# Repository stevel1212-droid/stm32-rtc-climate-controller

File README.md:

# stm32-rtc-climate-controller

Kicad project (Hardware) and Platform IO project (Firmware) of an STM32-based board climate controller utilizing an RTC module for time-scheduled environmental reading of temperature/humidity with SHT30 sensor and optional small relay for control.

I've ordered the PCBA (SMT assembly only) from JLCPCB and it costs around 62$  for 2 assembled and 3 empty boards with  coupon:

### 🛠️ Tools & Plugins Used:

#### Hardware (KiCad)
* **Footprints & Symbols:** To quickly download components from JLCPCB, I used the [easyeda2kicad](https://github.com/uPesy/easyeda2kicad.py) tool.
* **Manufacturing Files:** To create the fabrication files for PCB and SMD assembly via JLCPCB, I used the [kicad-jlcpcb-tools](https://github.com/bouni/kicad-jlcpcb-tools) external plugin.

#### Firmware (Software)
* **IDE:** Developed using [Visual Studio Code](https://code.visualstudio.com/) with the **PlatformIO IDE** extension.
* **Framework:** Written in C/C++ using the **Arduino Framework** for the STM32F103C8 microcontroller.
* **Peripherals:** Includes support for an SSD1306 OLED display using Adafruit libraries.

---

### 🛒 Hardware Components & Equipment Used:

If you want to build or debug this project, here is the specific hardware and equipment used:

* **Display:** [0.96 inch OLED I2C Display SSD1306](https://www.amazon.com/dp/B0D2RMQQHR?ref_=ppx_hzsearch_conn_dt_b_fed_asin_title_3) - Used for showing temperature, humidity, and time data.
* **RTC Battery:** [Energizer CR2032 Lithium Battery](https://www.amazon.com/dp/B009108SGS?ref=nb_sb_ss_w_as-reorder_k1_1_5&th=1) - Provides backup power to the RTC module to keep time when the main board is powered off.
* **Debugger:** [ST-Link V2 Programmer/Debugger](https://www.amazon.com/dp/B0C9PKJF2T?ref_=ppx_hzsearch_conn_dt_b_fed_asin_title_1&th=1) - Used for flashing the firmware and debugging the STM32.
* **Soldering Iron:** [Pinecil Smart Soldering Iron (BB2)](https://www.amazon.com/dp/B08PZBPXLZ?ref_=ppx_hzsearch_conn_dt_b_fed_asin_title_1&th=1) - Highly recommended portable soldering iron used for assembling the board.

## 🚀 First-Time Setup & Firmware Upload

Follow these steps to flash the firmware and configure the board for the first time:

### 1. Hardware Configuration (Boot Pins)
* Ensure that both **BOOT0** and **BOOT1** jumpers/pins are set to a **logic low** state (GND).

### 2. Connecting the Debugger
* Connect your **ST-Link V2** debugger to the **H1** connector on the board using the following pins: **SWDIO**, **SWCLK**, **3.3V**, and **GND**:

* ⚠️ **CRITICAL:** Do NOT connect the USB-C cable to the board while the debugger is connected and powering the system.

### 3. PlatformIO Configuration (`platformio.ini`)
Open your `platformio.ini` file and adjust the upload settings. You need to enable the ST-Link protocol and comment out the serial configurations:

```ini
# Set the upload protocol to ST-Link
upload_protocol = stlink

# Comment out the serial upload lines
; upload_protocol = serial
; upload_port = COM3
```

### 4. Flashing the Firmware
Plug the ST-Link V2 debugger into your computer's USB port.

In VS Code / PlatformIO, click the Upload button (the right-arrow icon in the bottom status bar) to flash the code to your STM32.

### 5. Setting the Date and Time (RTC Configuration)
Once the firmware is uploaded, disconnect the ST-Link V2 debugger from the board.

Connect the board to your computer using a USB-C cable.

Ensure you have the CP2102 driver installed on your computer so the USB-to-UART bridge is recognized.

Open the Serial Monitor in PlatformIO.

Send the current time and date through the serial terminal using the following exact format: HH:MM:SS DD:MM:YYYY (e.g., 14:30:00 15:06:2026).

### 🎁 Bonus: Serial Flashing (Alternative Method)
Note: This option is only available after the initial first-time flash.
If you prefer to flash future firmware updates directly via USB (Serial) instead of using the ST-Link debugger,
follow these steps:

* Set the BOOT0 pin/jumper to a logic high state (3.3V).
* Press the RESET button on the board to enter the embedded bootloader.
* In your platformio.ini file, switch the comments to enable serial upload:
```Ini
; upload_protocol = stlink
upload_protocol = serial
```
* Click the Upload button in PlatformIO.
* ⚠️ IMPORTANT: Once the upload is finished, you must set the BOOT0 pin back to a logic low state (GND) and press the RESET          button again. Otherwise, the newly uploaded program will not execute upon boot.

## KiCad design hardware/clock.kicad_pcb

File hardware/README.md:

here is the Kicad project files

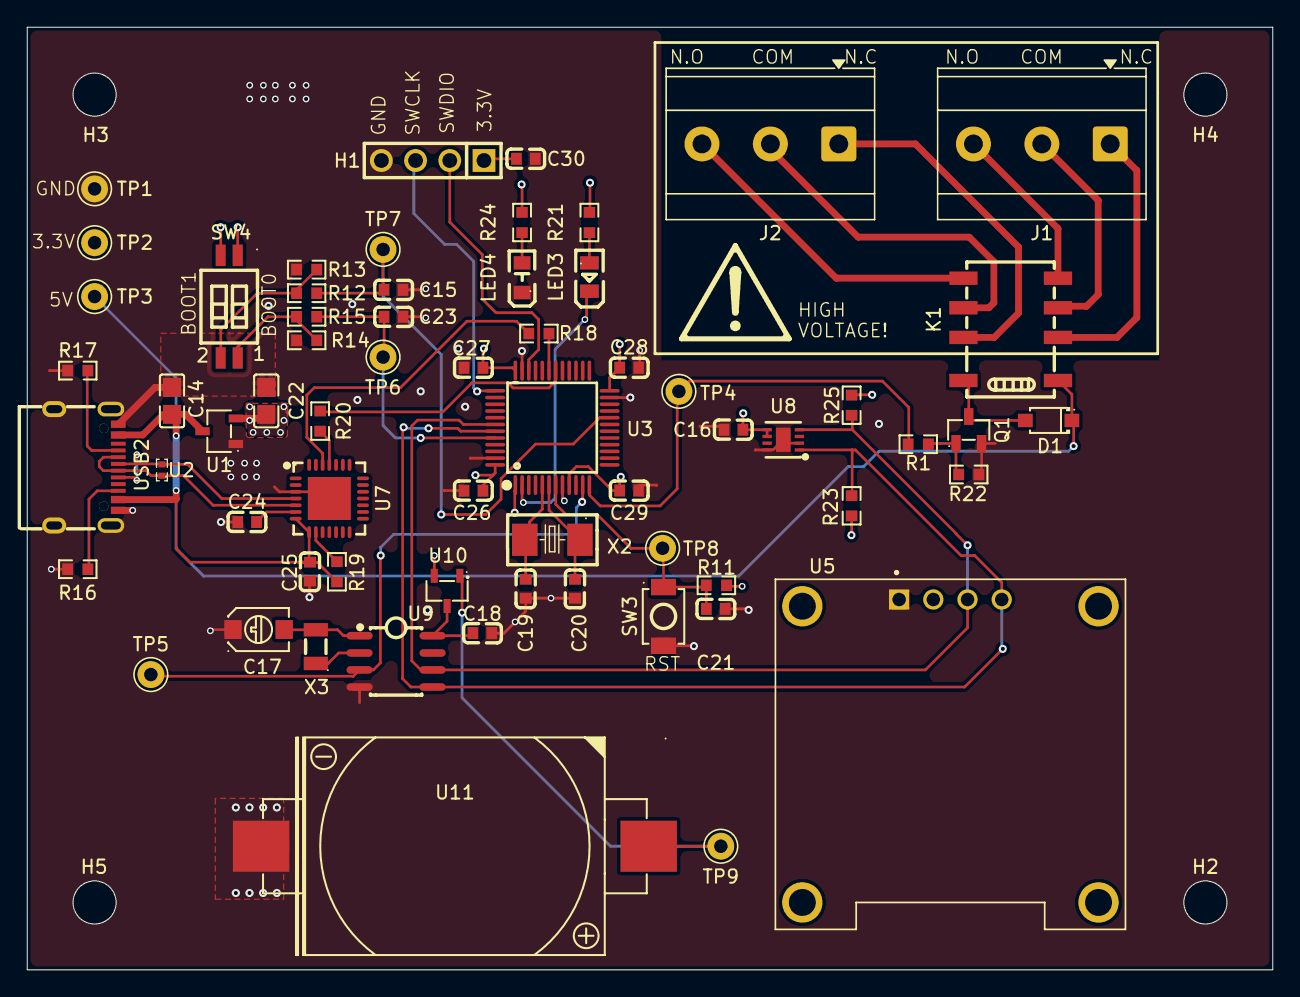
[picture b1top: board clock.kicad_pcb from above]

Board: 4 copper layers, 92.5 x 70.0 mm, 68 parts (0 on the bottom side), 41 nets.

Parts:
C14, C22: CL21B105KBFNNNE; C0805
C15, C16, C18, C21, C23, C24, C25, C26, C27, C28, C29, C30: CC0603KRX7R9BB104; C0603
C17: STC3MD20-T1; CAP-SMD_L4.5-W3.2_STC3MD20-T1
C19, C20: CL10C200JB8NNNC; C0603
D1: 1N4148W_C81598; SOD-123F_L2.7-W1.6-LS3.8-RD
H1: PZ254V-11-04P_C2691448; HDR-TH_4P-P2.54-V-M
H2, H3, H4, H5: MountingHole; MountingHole_3.2mm_M3
J1, J2: Screw_Terminal_01x03; TerminalBlock_MetzConnect_Type073_RT02603HBLU_1x03_P5.08mm_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
K1: G6K-2F-Y-DC5; RELAY-SMD_G6K-2F-X-XX
LED3: 0805G; LED0805-R-RD
LED4: FC-2012HRK-620D; LED0805-RD
Q1: 2N7002; SOT-23-3_L2.9-W1.3-P1.90-LS2.4-BR
R1: 0603WAF1000T5E; R0603
R11, R19: 0603WAF1002T5E; R0603
R12, R15, R18, R20, R21, R24: 0603WAF1001T5E; R0603
R13, R14, R22: 0603WAF1003T5E; R0603
R16, R17, R23, R25: 0603WAF5101T5E; R0603
SW3: TS-1088-AR02016; SW-SMD_L3.9-W3.0-P4.45
SW4: DSHP02TS-S; SW-SMD_DSHP02TS-S
TP1, TP2, TP3, TP4, TP5, TP6, TP7, TP8, TP9: TestPoint; Pin_D1.0mm_L10.0mm
U1: XC6206P332MR; SOT-23-3_L2.9-W1.6-P1.90-LS2.8-BR
U2: H3V3U10B; DFN1006-2L-BI
U3: STM32F103C8T6; LQFP-48_L7.0-W7.0-P0.50-LS9.0-BL
U5: DM-OLED096-636; MODULE_DM-OLED096-636
U7: CP2102-GMR; WQFN-28_L5.0-W5.0-P0.50-BL-EP3.2
U8: SHT30-DIS-B; DFN-8_L2.5-W2.5-P0.50-BL-EP
U9: PCF8563T/5,518; SOIC-8_L5.0-W4.0-P1.27-LS6.0-BL
U10: BAT54C_C22466350; SOT-23-3_L2.9-W1.3-P1.90-LS2.8-BR
U11: CR2032-BS-6; BAT-TH_CR2032-BS-6-1
USB2: TYPE-C 16PIN 2MD; USB-C-SMD_TYPE-C-6PIN-2MD-073
X2: X50328MSB2GI; CRYSTAL-SMD_L5.0-W3.2
X3: Q13FC1350000400; FC-135R_L3.2-W1.5

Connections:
+3.3V: C16.2, C22.2, C26.2, C27.2, C28.2, C29.2, C30.1, H1.1, R11.2, R21.2, R23.2, R24.2, R25.2, SW4.1, SW4.2, TP2.1 (1_1), U1.2 (Vout), U3.1 (VBAT), U3.9 (VDDA), U3.24 (VDD_1), U3.36 (VDD_2), U3.48 (VDD_3), U5.2 (VCC_IN), U8.5 (VDD), U8.6 (nRESET), U10.2 (A)
+5V: C14.2, C25.2, D1.1 (K), K1.1, R19.1, TP3.1 (1_1), U1.3 (Vin), U7.7 (REGIN), U7.8 (VBUS), USB2.2 (VBUS), USB2.11 (VBUS)
/mcu/BOOT0: C23.2, R15.2, TP6.1 (1_1), U3.44 (BOOT0)
/mcu/BOOT1: C15.2, R12.1, TP7.1 (1_1), U3.20 (PB2)
/mcu/DN: U2.1, U7.5 (D-), USB2.5 (DN2), USB2.7 (DN1)
/mcu/DP: U2.2, U7.4 (D+), USB2.6 (DP1), USB2.8 (DP2)
/mcu/NRST: C21.2, R11.1, SW3.2, TP8.1 (1_1), U3.7 (NRST)
/mcu/OSC_IN: C19.2, U3.5 (PD0-OSC_IN), X2.2 (OSC2)
/mcu/OSC_OUT: C20.2, U3.6 (PD1-OSC_OUT), X2.1 (OSC1)
/mcu/PA1: TP5.1 (1_1), U3.11 (PA1), U9.3 (~INT)
/mcu/PA2: R1.1, TP4.1 (1_1), U3.12 (PA2)
/mcu/PA9: R20.2, U3.30 (PA9)
/mcu/PA10: R18.2, U3.31 (PA10)
/mcu/PC13: LED3.2 (K), U3.2 (PC13-TAMPER-RTC)
/mcu/SCL: R25.1, U3.42 (PB6), U5.3 (SCL), U8.4 (SCL), U9.6 (SCL)
/mcu/SDA: R23.1, U3.43 (PB7), U5.4 (SDA), U8.1 (SDA), U9.5 (SDA)
/mcu/SWCLK: H1.3, U3.37 (PA14)
/mcu/SWIO: H1.2, U3.34 (PA13)
GND: C14.1, C15.1, C16.1, C17.1, C18.1, C19.1, C20.1, C21.1, C22.1, C23.1, C24.1, C25.1, C26.1, C27.1, C28.1, C29.1, C30.2, H1.4, LED4.1 (-), Q1.2 (S), R13.1, R14.1, R16.2, R17.2, R22.1, SW3.1, TP1.1 (1_1), U1.1 (GND), U3.8 (VSSA), U3.23 (VSS_1), U3.35 (VSS_2), U3.47 (VSS_3), U5.1 (GND), U7.3 (GND), U7.29 (EP), U8.2 (ADDR), U8.8 (VSS), U8.9 (EPAD), U9.4 (VSS), U11.2, USB2.1 (GND), USB2.12 (GND), USB2.13 (SHELL), USB2.14 (SHELL)
unnamed: D1.2 (A), K1.8, Q1.3 (D)
unnamed: J1.1, K1.2
unnamed: J1.2, K1.3
unnamed: J1.3, K1.4
unnamed: J2.1, K1.7
unnamed: J2.2, K1.6
unnamed: J2.3, K1.5
unnamed: LED3.1 (A), R21.1
unnamed: LED4.2 (+), R24.1
unnamed: Q1.1 (G), R1.2, R22.2
unnamed: R12.2, R13.2, SW4.3
unnamed: R14.2, R15.1, SW4.4
unnamed: TP9.1 (1_1), U10.1 (A), U11.1
unnamed: R20.1, U7.25 (RXD)
unnamed: R18.1, U7.26 (TXD)
unnamed: C24.2, U7.6 (VDD)
unnamed: R19.2, U7.9 (~RST)
unnamed: C17.2, U9.1 (OSCI), X3.2
unnamed: U9.2 (OSCO), X3.1
unnamed: C18.2, U9.8 (VDD), U10.3 (K)
unnamed: R17.1, USB2.4 (CC1)
unnamed: R16.1, USB2.10 (CC2)

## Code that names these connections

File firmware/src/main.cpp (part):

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#define SCREEN_WIDTH 128 
#define SCREEN_HEIGHT 64

#define LED_PIN PC13
#define RELAY_PIN PA2
#define PCF8563_ADDR 0x51      // RTC I2C address
#define SHT30_ADDR 0x44         // Temperature sensor I2C address

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
void setup() {
  // put your setup code here, to run once:
  Serial.setTx(PA9); // מגדיר את המשדר של הבקר לפין PA10 (היכן שחיברת את ה-RX של ה-USB)
  Serial.setRx(PA10);  // מגדיר את הקולט של הבקר לפין PA9 (היכן שחיברת את ה-TX של ה-USB)
  Serial.begin(115200);
  delay(1000);
  
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  pinMode(LED_PIN, OUTPUT);
  pinMode(RELAY_PIN, OUTPUT);
  digitalWrite(RELAY_PIN, LOW);  // Default relay OFF
  Wire.setSDA(PB7);
  Wire.setSCL(PB6);
  Wire.begin();
  
  if(!display.begin(SSD1306_SWITCHCAPVCC, 0x3C))
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
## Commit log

2026-06-15 Add MIT License to the project
2026-06-15 Add README for Kicad project files
2026-06-15 Add initial README for Platform IO project
2026-06-15 Enhance README with project details and tools
    Added detailed project description and tools/plugins used.
2026-06-15 Update README with RTC battery details and tools
    Added RTC battery information and updated tools list.
2026-06-16 Update README with setup and firmware upload instructions
    Added first-time setup instructions and hardware configuration details for firmware upload.
2026-06-16 Update README with PlatformIO configuration instructions
2026-06-16 Modify README for ST-Link upload protocol instructions
    Updated PlatformIO configuration instructions for ST-Link.
2026-06-16 Add serial flashing instructions to README
    Added instructions for serial flashing as an alternative method for firmware updates.
2026-06-16 Format bonus section for serial flashing instructions
